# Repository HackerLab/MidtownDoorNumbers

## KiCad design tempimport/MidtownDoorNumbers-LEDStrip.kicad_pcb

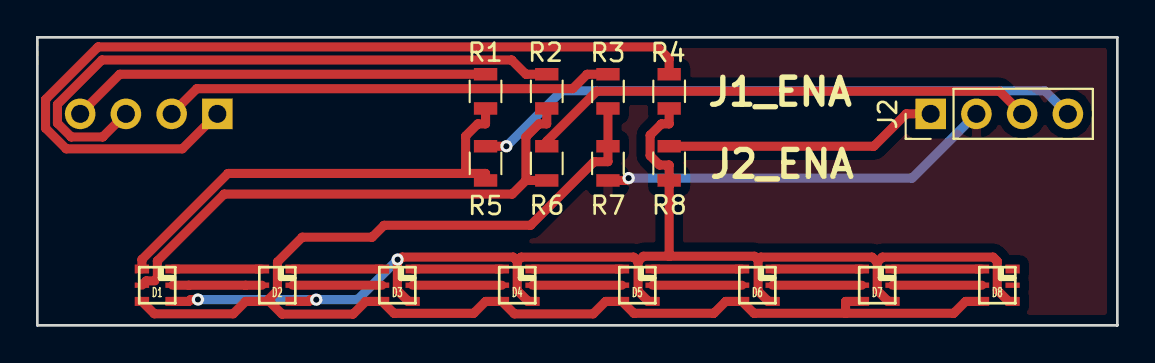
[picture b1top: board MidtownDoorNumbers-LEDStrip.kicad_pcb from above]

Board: 2 copper layers, 60.0 x 16.0 mm, 18 parts (1 on the bottom side), 26 nets.

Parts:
D1, D2, D3, D4, D5, D6, D7, D8: APA102; APA102-2020
J1, J2: CONN_01X04; Pin_Header_Straight_1x04_Pitch2.54mm
R1, R2, R3, R4, R5, R6, R7, R8: 0; R_0805

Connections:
unnamed: D1.1, D2.2
unnamed: D1.2, R1.1, R5.2
unnamed: D1.3, R2.1, R6.2
unnamed: D1.4, D2.4, D3.4, D4.4, D5.4, D6.4, D7.4, D8.4, R3.1, R7.2
unnamed: D1.5, D2.5, D3.5, D4.5, D5.5, D6.5, D7.5, D8.5, R4.1, R8.2
unnamed: D1.6, D2.3
unnamed: D2.1, D3.2
unnamed: D2.6, D3.3
unnamed: D3.1, D4.2
unnamed: D3.6, D4.3
unnamed: D4.1, D5.2
unnamed: D4.6, D5.3
unnamed: D5.1, D6.2
unnamed: D5.6, D6.3
unnamed: D6.1, D7.2
unnamed: D6.6, D7.3
unnamed: D7.1, D8.2
unnamed: D7.6, D8.3
unnamed: J1.1, R4.2
unnamed: J1.2, R3.2
unnamed: J1.3, R2.2
unnamed: J1.4, R1.2
unnamed: J2.1, R8.1
unnamed: J2.2, R7.1
unnamed: J2.3, R6.1
unnamed: J2.4, R5.1

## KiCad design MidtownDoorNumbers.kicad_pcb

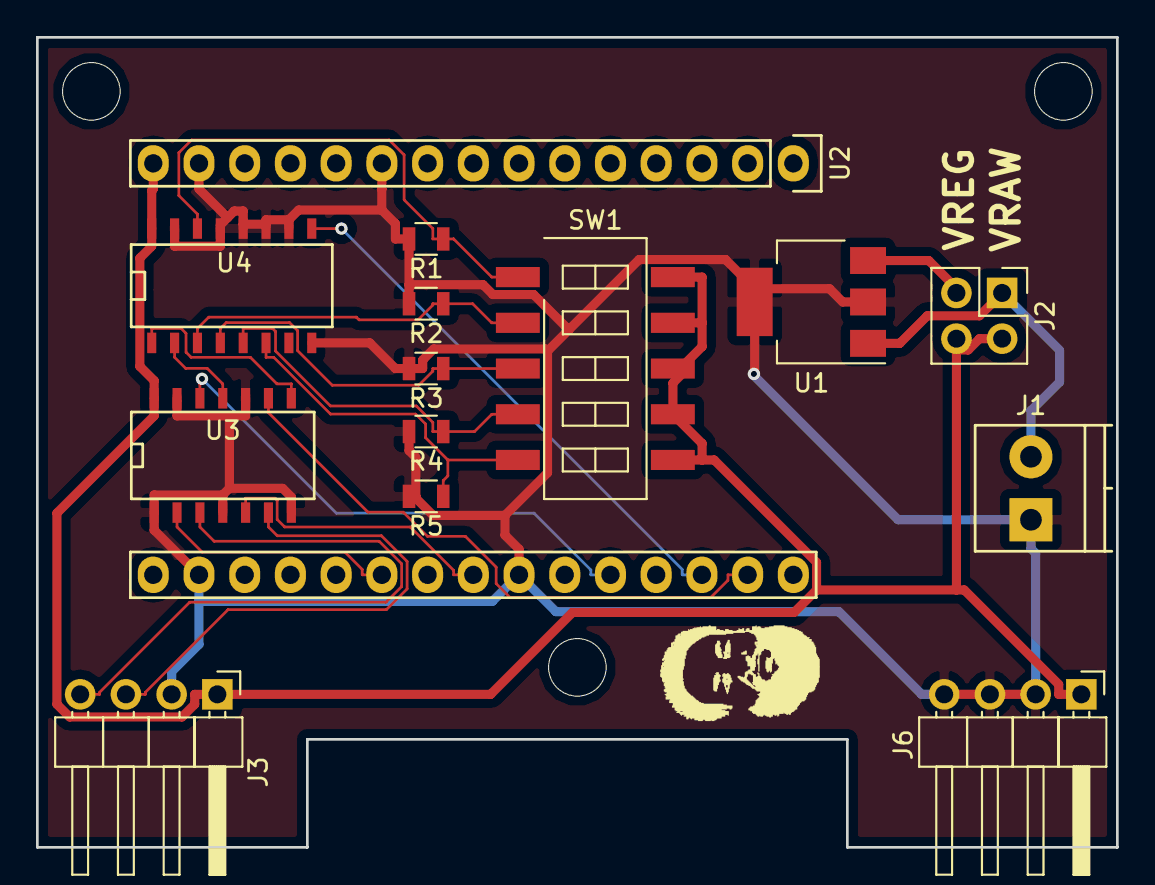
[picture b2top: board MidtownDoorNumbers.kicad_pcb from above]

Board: 2 copper layers, 60.0 x 45.0 mm, 19 parts (1 on the bottom side), 18 nets.

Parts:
J1: CONN_01X02; TerminalBlock_Pheonix_PT-3.5mm_2pol
J2: CONN_02X02; Pin_Header_Straight_2x02_Pitch2.54mm
J3, J6: CONN_01X04; Pin_Header_Angled_1x04_Pitch2.54mm
R1, R2, R3, R4, R5: 10K; R_0805
REFBC: MountingHole_3.2mm_M3
REFMTR: MountingHole_3.2mm_M3
REFTL: MountingHole_3.2mm_M3
SW1: SW_DIP_x05; SW_DIP_x5_W8.61mm_Slide_LowProfile
U1: LM7805CT; SOT-223-3Lead_TabPin2
U2: NodeMCU_Amica_R2
U3: 74AHC125; SOIC-14_N
U4: 74HC165; SO-16-N
nilesface: nilesface_smaller
nilesface#2: nilesface_smaller

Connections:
5VDC: J2.2, J2.4, J3.1, J6.1, SW1.6, SW1.7, SW1.8, SW1.9, SW1.10, U2.15, U3.14, U4.16
GND: J1.1, J3.2, J6.2, J6.3, J6.4, R1.2, R2.2, R3.2, R4.2, R5.2, U1.2, U2.10, U2.14, U2.17, U2.24, U3.1, U3.4, U3.7, U3.10, U3.13, U4.8, U4.10, U4.11, U4.12, U4.13, U4.15
LCLK: U2.23, U3.5
LCLK5: J3.3, U3.6
MOSI: U2.21, U3.2
MOSI5: J3.4, U3.3
unnamed: J1.2, J2.1, U1.1
unnamed: J2.3, U1.3
SEL_0: R1.1, SW1.1, U4.14
SEL_1: R2.1, SW1.2, U4.3
SEL_2: R3.1, SW1.3, U4.4
SEL_3: R4.1, SW1.4, U4.5
SEL_4: R5.1, SW1.5, U4.6
SH/~LD: U2.29, U3.9
SH/~LD~5: U3.8, U4.1
SHCLK: U2.26, U3.12
SHCLK5: U3.11, U4.2
SHOUT: U2.28, U4.9

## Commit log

2019-06-15 init
2019-06-19 technically fabbable
2019-06-21 Generated Gerbers
2019-06-29 stencilwork
2019-06-29 third attempt
